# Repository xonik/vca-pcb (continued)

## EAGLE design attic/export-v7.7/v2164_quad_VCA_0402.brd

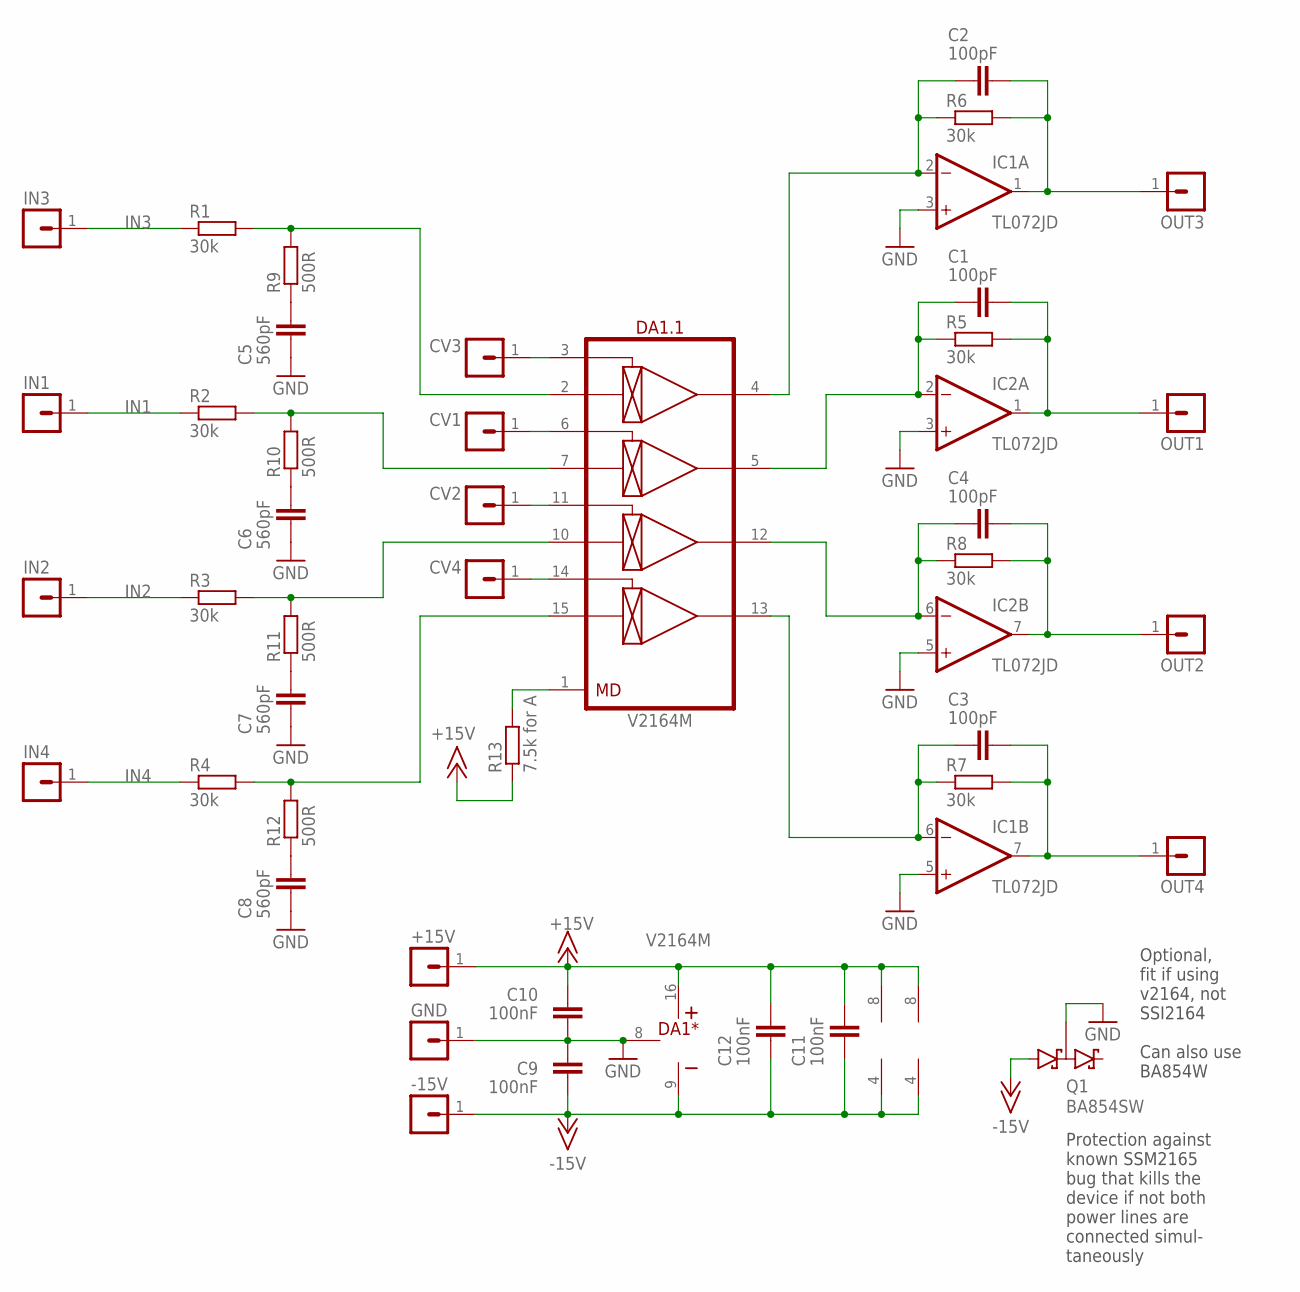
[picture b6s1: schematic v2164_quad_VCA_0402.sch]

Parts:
+15V: MA01-1JN; MA01N-1J
-15V: MA01-1JN; MA01N-1J
C1, C2, C3, C4: 100pF; C0402
C5, C6, C7, C8: 560pF; C0603
C9, C10, C11, C12: 100nF; C0402
CV1, CV2, CV3, CV4: MA01-1JN; MA01N-1J
DA1: V2164M; SO-16
GND: MA01-1JN; MA01N-1J
IC1, IC2: TL072JD; SO08J
IN1, IN2, IN3, IN4: MA01-1JN; MA01N-1J
OUT1, OUT2, OUT3, OUT4: MA01-1JN; MA01N-1J
Q1: BA854SW; SOT23-3J
R1, R2, R3, R4, R5, R6, R7, R8: 30k; R0402
R9, R10, R11, R12: 500R; R0402
R13: 7.5k for A; R0402

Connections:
+15V: +15V.1, C10.2, C11.2, C12.2, DA1.16 (V+), IC1.8 (V+), IC2.8 (V+), R13.1
-15V: -15V.1, C9.1, C11.1, C12.1, DA1.9 (V-), IC1.4 (V-), IC2.4 (V-), Q1.1 (A1)
CV1: CV1.1, DA1.6 (CV2)
CV2: CV2.1, DA1.11 (CV3)
CV3: CV3.1, DA1.3 (CV1)
CV4: CV4.1, DA1.14 (CV4)
GND: C5.1, C6.1, C7.1, C8.1, C9.2, C10.1, DA1.8 (GND), GND.1, IC1.3 (+IN), IC1.5 (+IN), IC2.3 (+IN), IC2.5 (+IN), Q1.3 (K1A2)
IN1: IN1.1, R2.1
IN2: IN2.1, R3.1
IN3: IN3.1, R1.1
IN4: IN4.1, R4.1
unnamed: C4.1, DA1.12 (OUT3), IC2.6 (-IN), R8.1
unnamed: DA1.1 (MD), R13.2
unnamed: C3.1, DA1.13 (OUT4), IC1.6 (-IN), R7.1
unnamed: C2.1, DA1.4 (OUT1), IC1.2 (-IN), R6.1
unnamed: C1.1, DA1.5 (OUT2), IC2.2 (-IN), R5.1
unnamed: C5.2, R9.1
unnamed: C6.2, R10.1
unnamed: C7.2, R11.1
unnamed: C8.2, R12.1
unnamed: DA1.2 (IN1), R1.2, R9.2
unnamed: DA1.7 (IN2), R2.2, R10.2
unnamed: DA1.10 (IN3), R3.2, R11.2
unnamed: DA1.15 (IN4), R4.2, R12.2
OUT1: C1.2, IC2.1 (OUT), OUT1.1, R5.2
OUT2: C4.2, IC2.7 (OUT), OUT2.1, R8.2
OUT3: C2.2, IC1.1 (OUT), OUT3.1, R6.2
OUT4: C3.2, IC1.7 (OUT), OUT4.1, R7.2

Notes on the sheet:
Optional, fit if using v2164, not SSI2164 Can also use BA854W
Protection against known SSM2165 bug that kills the device if not both power lines are connected simul- taneously

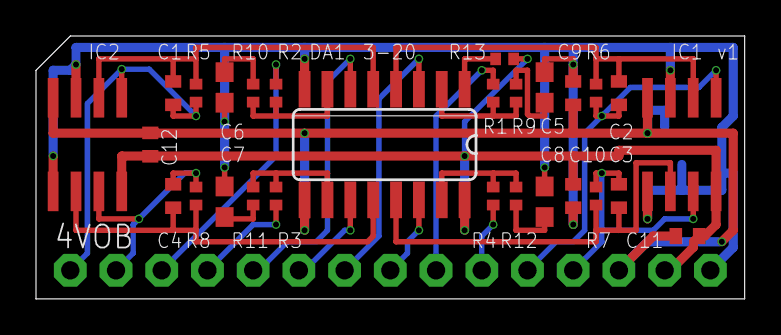
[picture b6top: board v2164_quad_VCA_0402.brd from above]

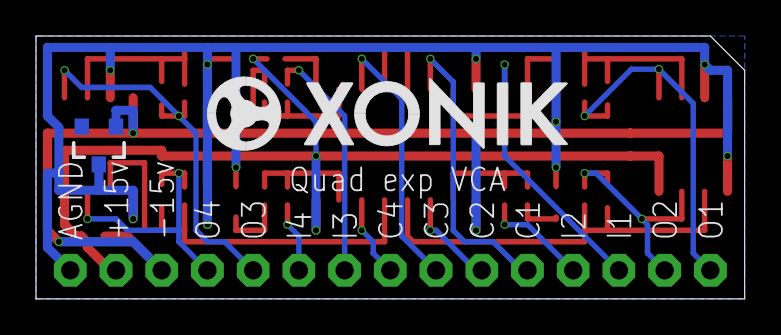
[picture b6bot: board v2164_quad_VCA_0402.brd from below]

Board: 2 copper layers, 39.4 x 14.6 mm, 45 parts (2 on the bottom side), 28 nets.

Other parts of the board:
U$1: XONIK_LOGO_20

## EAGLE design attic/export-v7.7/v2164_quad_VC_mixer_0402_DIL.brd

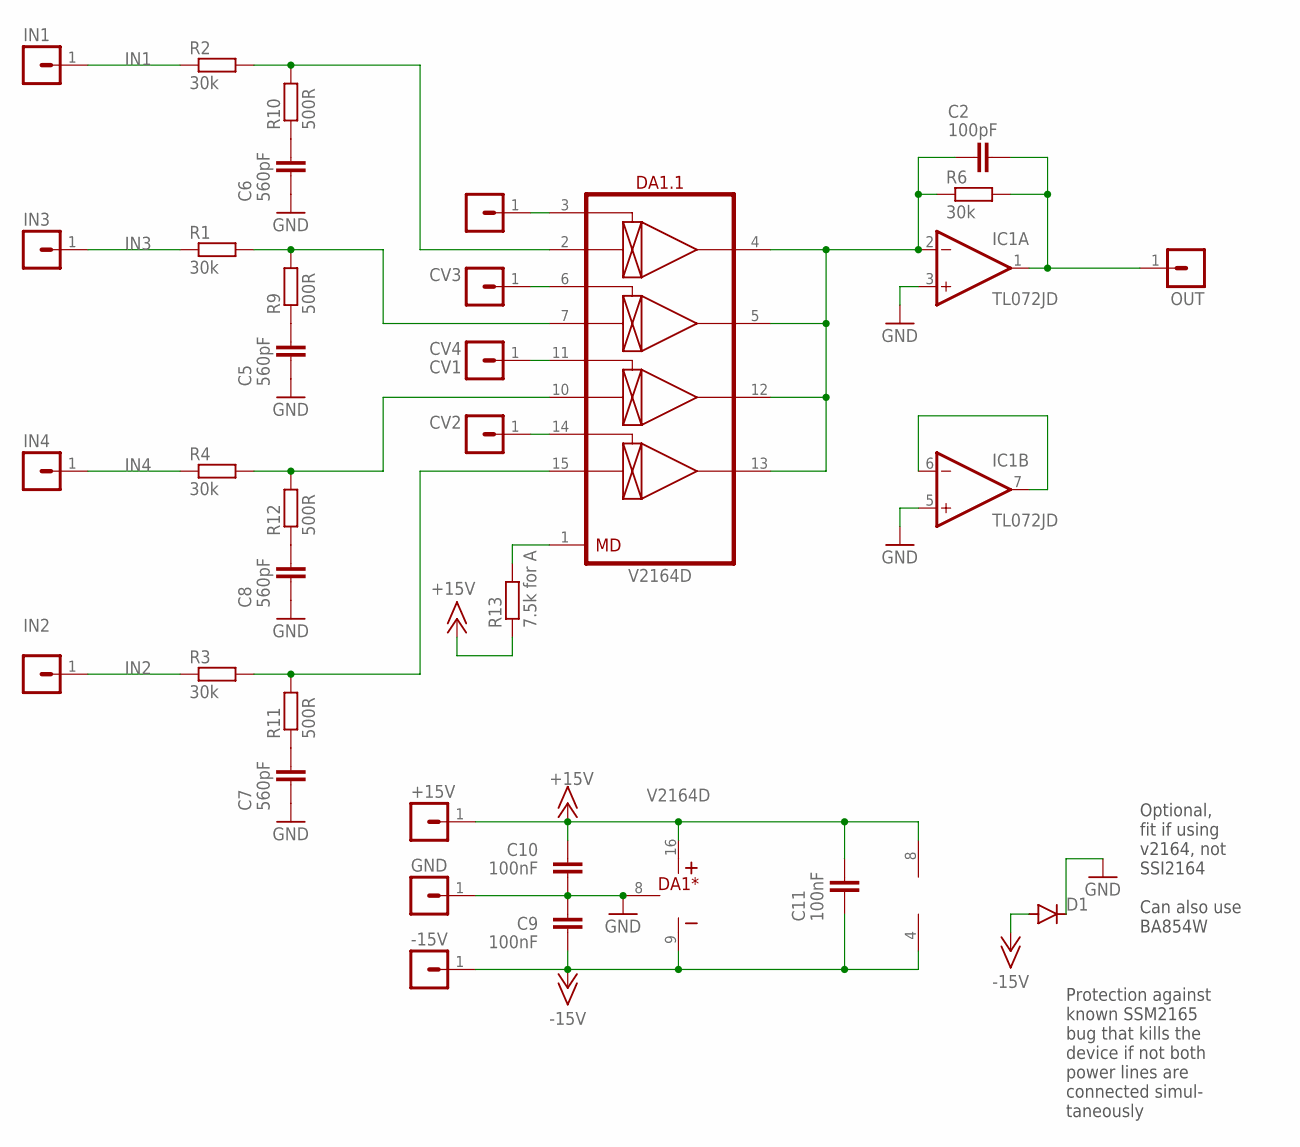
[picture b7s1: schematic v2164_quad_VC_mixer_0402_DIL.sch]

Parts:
+15V: MA01-1JP; SIP-PIN01-1J
-15V: MA01-1JP; SIP-PIN01-1J
C2: 100pF; C0402
C5, C6, C7, C8: 560pF; C0603
C9, C10, C11: 100nF; C0402
CV1, CV2, CV3, CV4: MA01-1JP; SIP-PIN01-1J
D1: DIODE-SOD323-R; SOD323-R
DA1: V2164D; DIP-16
GND: MA01-1JP; SIP-PIN01-1J
IC1: TL072JD; SO08J
IN1, IN2, IN3, IN4: MA01-1JP; SIP-PIN01-1J
OUT: MA01-1JP; SIP-PIN01-1J
R1, R2, R3, R4, R6: 30k; R0402
R9, R10, R11, R12: 500R; R0402
R13: 7.5k for A; R0402

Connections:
+15V: +15V.1, C10.2, C11.2, DA1.16 (V+), IC1.8 (V+), R13.1
-15V: -15V.1, C9.1, C11.1, D1.A, DA1.9 (V-), IC1.4 (V-)
GND: C5.1, C6.1, C7.1, C8.1, C9.2, C10.1, D1.C, DA1.8 (GND), GND.1, IC1.3 (+IN), IC1.5 (+IN)
IN1: IN1.1, R2.1
IN2: IN2.1, R3.1
IN3: IN3.1, R1.1
IN4: IN4.1, R4.1
unnamed: DA1.1 (MD), R13.2
unnamed: CV1.1, DA1.3 (CV1)
unnamed: CV3.1, DA1.6 (CV2)
unnamed: CV2.1, DA1.14 (CV4)
unnamed: C5.2, R9.1
unnamed: C6.2, R10.1
unnamed: C7.2, R11.1
unnamed: C8.2, R12.1
unnamed: CV4.1, DA1.11 (CV3)
unnamed: C2.1, DA1.4 (OUT1), DA1.5 (OUT2), DA1.12 (OUT3), DA1.13 (OUT4), IC1.2 (-IN), R6.1
unnamed: DA1.7 (IN2), R1.2, R9.2
unnamed: DA1.2 (IN1), R2.2, R10.2
unnamed: DA1.15 (IN4), R3.2, R11.2
unnamed: DA1.10 (IN3), R4.2, R12.2
OUT3: C2.2, IC1.1 (OUT), OUT.1, R6.2
OUT4: IC1.6 (-IN), IC1.7 (OUT)

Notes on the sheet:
Optional, fit if using v2164, not SSI2164 Can also use BA854W
Protection against known SSM2165 bug that kills the device if not both power lines are connected simul- taneously

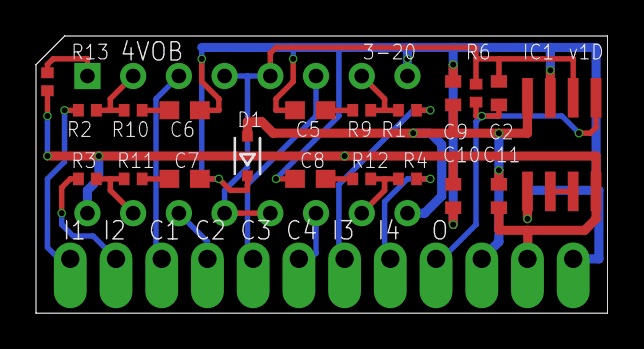
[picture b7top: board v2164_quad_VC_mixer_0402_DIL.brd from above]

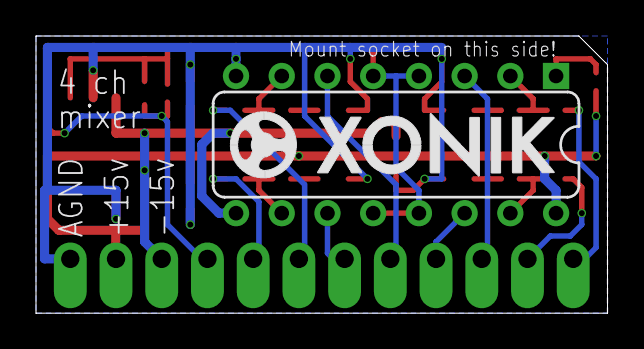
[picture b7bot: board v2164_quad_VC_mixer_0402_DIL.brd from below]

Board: 2 copper layers, 31.8 x 15.4 mm, 34 parts (2 on the bottom side), 23 nets.

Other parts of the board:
U$1: XONIK_LOGO_18

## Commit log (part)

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2017-09-08 Initial commit, moved contents from google drive
2018-07-24 New linear VCA with external trimmers for symmetry and gain
2020-02-26 Added git ignore
2020-03-13 Routed v2164-based quad VCA
2020-03-13 Finished routing 0402 version without supply line protection
2020-03-13 Added ground plane
2020-03-14 Made mixer and added top labels
2020-03-14 Finished top layer on both boards i think
2020-03-14 Completed silkscreen and routing on both vca and mixer.
2020-03-14 Added optional shottky diodes
2020-03-14 Created DIL version of VCA
2020-03-14 Added DIL version of quad mixer
2020-03-23 Fixed some silk screen errors and replaced pads with some that solder slightly better
2020-03-24 Changed diode to B5817 (1n5817) as BAT854 is not available at JLCPCB
2020-03-24 Tiny placement tweak
2020-03-25 Added mixing point to mixer for external input
2020-03-25 Checked BOM for vca
2020-03-25 Added DIL version of mixer w ext
2021-03-15 Added AS3364 versions of quad VCA
2021-03-16 Turned pads to make it possible to solder angled legs
2022-01-18 AS3364 based waveshape mixer
2022-01-19 Finished waveshape mixer and fixed a serious bug
2022-01-20 Checked most things, changed CV input resistors, added cap to mixer output
2022-01-22 Panelizing AS3364 boards
2022-01-22 Panelized AS3364
2022-01-22 Almost finished bom/cpl
2022-01-23 Ready to order I think
2022-04-08 moving
2022-05-24 Added a waveform mixer for VCO as well
2023-08-02 Working on bus mixer with CH446Q crosspoint switch
2023-08-03 Tracing the bus mixer
2023-08-04 Most of lower part traced ok
2023-08-05 Missing 12V to left side only
2023-08-05 all traced
2023-08-05 Reordered lines to make coding easier
2023-08-05 Added 220k resistors to bus
2023-08-06 Switched to 16x2 connector
2023-08-07 Working on v2.0
2023-08-08 Traced new lines for bus mixer v2.0, missing lines under CH446Q
2023-08-08 Finished tracing v2.0 of bus mixer
2023-08-08 Tiny tweak
2023-08-09 Fixed CH446Q footprint bug for v1.0 of bus mixer
2023-08-14 Ordered 10 bus mixer v2.0
2023-08-23 Fixed error where bus instead of sum was output
2023-09-13 Placed all components close to correct
2023-09-13 Mixer change, not sure what
2023-09-15 Finished tracing switches and vcas internally
2023-09-15 Digital lines traced
2023-09-15 Moved dry/wet bus mixer to center to shorten vca-switch distances
2023-09-16 Almost all signals routed except outputs
2023-09-17 Mostly traced, need to do ground and cleanup
2023-09-17 Finished tracing, need part numbers
2023-09-18 Only need to fix text
2023-09-18 All labels and names fixed
2023-09-18 Replaced connectors
2023-09-19 Added sum a and b to output pins
2023-09-25 New version with inverted vcas on inputs
2023-09-26 Fixed pin labeling
2023-09-29 Completed bom for AS3364 DG412 bus mixer
2023-09-29 Fixed overlap
2023-09-29 Updated gerber after discovery of error
2023-09-29 TODO about needing to invert output
2023-11-29 Added v1.1 bus mixer, not finished routing
2023-11-29 Finished tracing v1.1 of DG412 bus mixer
2023-12-03 Tested bom ok
2023-12-05 Changed logic voltage resistor divider
2023-12-25 Split 32p into 2 x 16p to use more standard parts
2023-12-25 Moved corner to origo
2023-12-26 Updated pin spacing to 2.54mm to still fit breadboard
2023-12-26 A slight ground plane fix
2024-03-02 v1.3 introduces SVF chain input
2024-05-24 Ready to try with mainboard
2024-05-26 Cleanup
2024-05-28 Changed connector values
2024-06-03 Updated decoupling caps. Tested with JLCPCB
2024-06-04 Added screw holes
2024-06-06 Fixed extended resistor
2024-06-22 Added increase-gain resistor to noise input
2024-06-23 Angled bus board connector added
2024-06-23 Switched to female pin headers
2024-06-23 v1.0 ready for production
2024-06-23 Fixed two airwires
2024-06-25 Increased via outer diameter
2024-06-25 Fixed weird airwire
2025-01-30 Traced v1.4
2025-01-30 v1.4 4 layer - everything connected, only slight dimension issue. Still need vias
2025-01-31 Added better decoupling caps
2025-01-31 Better silk screen
2025-01-31 Lots of vias
2025-01-31 Finished v1.4 4 layer
2025-02-05 Routed chain inverter
2025-03-01 Preparing 4 layer for production
2025-12-21 export v7
